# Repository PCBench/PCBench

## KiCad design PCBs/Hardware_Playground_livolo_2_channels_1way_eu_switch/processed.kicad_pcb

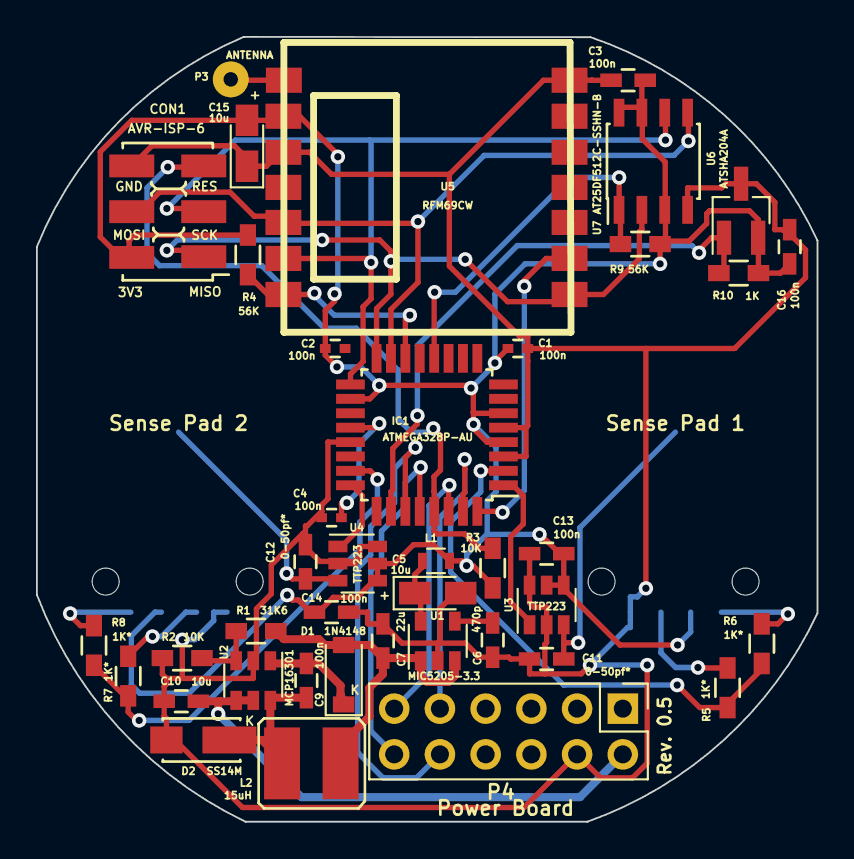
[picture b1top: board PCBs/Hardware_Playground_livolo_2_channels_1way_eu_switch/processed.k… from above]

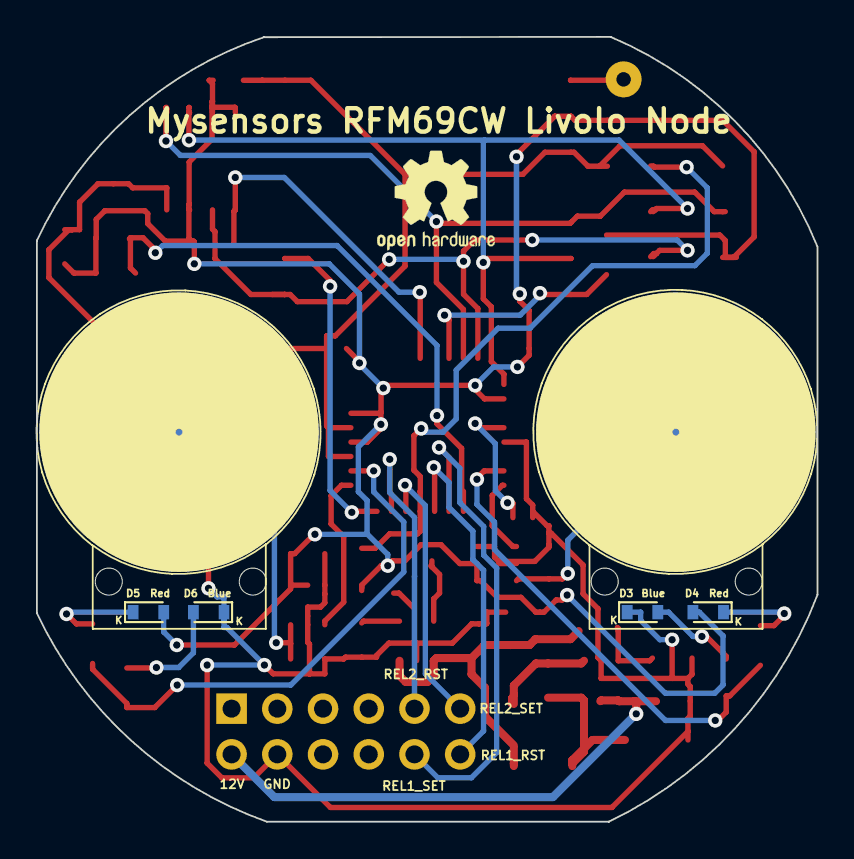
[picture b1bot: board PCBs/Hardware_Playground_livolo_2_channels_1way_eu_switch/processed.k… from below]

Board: 2 copper layers, 43.4 x 43.6 mm, 46 parts (4 on the bottom side), 33 nets.

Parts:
C1, C2, C4: 100n; C_0402
C3, C9, C13, C14, C16: 100n; C_0603_HandSoldering
C5, C15: 10u; CP_Tantalum_Case-R_EIA-2012-12_Wave
C6: 470p; C_0603_HandSoldering
C7: 22u; C_0603_HandSoldering
C10: 10u; C_0603_HandSoldering
C11, C12: 0-50pf*; C_0603_HandSoldering
CON1: AVR-ISP-6; AVR_ISP_SMT_Small_02x03
D1: 1N4148; SOD-123
D2: SS14M
D3, D6: Blue; D_0603
D4, D5: Red; D_0603
IC1: ATMEGA328P-AU; TQFP-32_7x7mm_Pitch0.8mm
L1: BLM18HE152SN1D; R_0603
L2: 15uH; VLCF4020T-150MR68
P1: Sense Pad 1; touch_pad_16mm
P2: Sense Pad 2; touch_pad_16mm
P3: ANTENNA; SolderWirePad_single_0-8mmDrill
P4: Power Board; Pin_Header_Straight_2x06_Pitch2.54mm
R1: 31K6; R_0603_HandSoldering
R2, R3: 10K; R_0603_HandSoldering
R4, R9: 56K; R_0603_HandSoldering
R5, R6, R7, R8: 1K*; R_0603_HandSoldering
R10: 1K; R_0603_HandSoldering
U1: MIC5205-3.3; SOT-23-5
U2: MCP16301; SOT-23-6
U3, U4: TTP223; SOT-23-6
U5: RFM69CW
U6: AT25DF512C-SSHN-B; SOIC-8_3.9x4.9mm_Pitch1.27mm
U7: ATSHA204A; SOT-23_Handsoldering

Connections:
+3V3: C1.1, C2.2, C3.2, C13.1, C14.1, C15.2, C16.2, CON1.2, D4.2, D5.2, IC1.4, IC1.6, IC1.18, L1.1, R3.1, R4.2, R9.1, R10.1, U3.4, U3.5, U4.4, U4.5, U5.2, U6.3, U6.7, U6.8, U7.2
/12Vcc: C10.1, P4.2, U2.4, U2.5
/ATSHA204A: IC1.26, R10.2, U7.1
/FLASH_SS: IC1.12, R9.2, U6.1
/INT: IC1.32, U5.9
/MISO: CON1.1, IC1.16, U5.8, U6.2
/MOSI: CON1.4, IC1.15, U5.5, U6.5
/RADIO_SS: IC1.14, R4.1, U5.7
/RESET: CON1.5, IC1.29, R3.2
/Relay1_Reset: IC1.28, P4.12
/Relay1_Set: IC1.27, P4.10
/Relay2_Reset: IC1.31, P4.9
/Relay2_Set: IC1.30, P4.11
/S1_LEDs: IC1.2, R5.2, R6.2
/S2_LEDs: IC1.23, R7.2, R8.2
/SCK: CON1.3, IC1.17, U5.6, U6.6
/TS1: IC1.1, U3.1
/TS2: IC1.24, U4.1
GND: C1.2, C3.1, C4.1, C5.2, C6.2, C7.2, C10.2, C11.2, C12.2, C13.2, C14.2, C15.1, C16.1, CON1.6, D2.2, D3.1, D6.1, IC1.3, IC1.5, IC1.21, P4.4, R2.1, U1.2, U2.2, U3.2, U3.6, U4.2, U4.6, U5.3, U5.14, U6.4, U7.3
unnamed: C4.2, IC1.20
unnamed: C5.1, L1.2, U1.5
unnamed: C6.1, U1.4
unnamed: C7.1, D1.2, L2.1, R1.2, U1.1, U1.3
unnamed: C9.1, D1.1, U2.1
unnamed: C9.2, D2.1, L2.2, U2.6
unnamed: C11.1, P1.1, U3.3
unnamed: C12.1, P2.1, U4.3
unnamed: D3.2, R7.1
unnamed: D4.1, R8.1
unnamed: D5.1, R6.1
unnamed: D6.2, R5.1
unnamed: P3.1, U5.1
unnamed: R1.1, R2.2, U2.3

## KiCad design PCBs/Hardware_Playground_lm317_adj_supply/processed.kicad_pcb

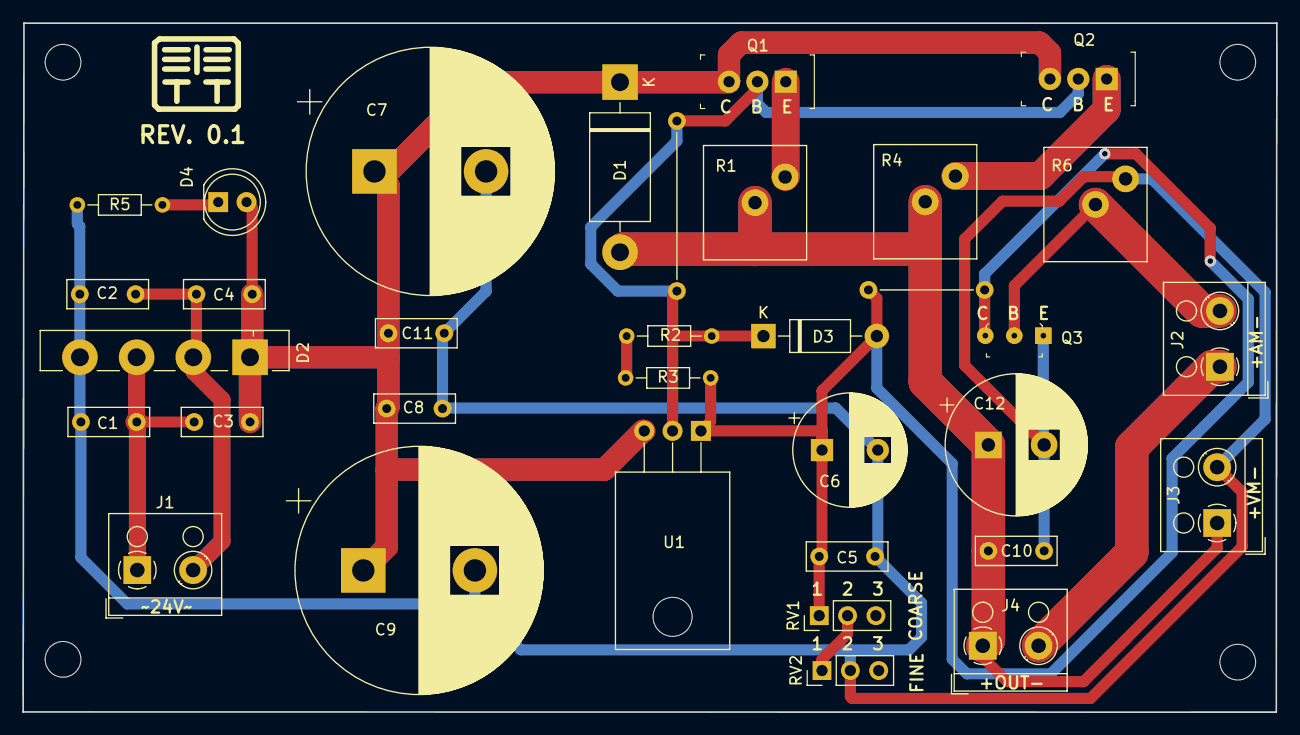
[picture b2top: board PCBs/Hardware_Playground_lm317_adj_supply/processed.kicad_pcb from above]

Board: 2 copper layers, 112.3 x 61.7 mm, 32 parts (0 on the bottom side), 14 nets.

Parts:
C1, C2, C3, C4, C5, C8, C10, C11: 0.1u/63V; C_Rect_L7.2mm_W2.5mm_P5.00mm_FKS2_FKP2_MKS2_MKP2
C6: 150u/50V; CP_Radial_D10.0mm_P5.00mm
C7, C9: 3300u/50V; CP_Radial_D22.0mm_P10.00mm_SnapIn
C12: 1000u/50V; CP_Radial_D12.5mm_P5.00mm
D1: MUR420; D_DO-201AD_P15.24mm_Horizontal
D2: GBU8M; Diode_Bridge_Vishay_GBU
D3: 1N4007; D_DO-41_SOD81_P10.16mm_Horizontal
D4: PWR_LED; LED_D5.0mm
J1: TR(24Vac); TerminalBlock_RND_205-00001_1x02_P5.00mm_Horizontal
J2: AMP_MEAS; TerminalBlock_RND_205-00001_1x02_P5.00mm_Horizontal
J3: VOLT_MEAS; TerminalBlock_RND_205-00001_1x02_P5.00mm_Horizontal
J4: V_REG_OUT; TerminalBlock_RND_205-00001_1x02_P5.00mm_Horizontal
Q1, Q2: TIP41C; TO-220-3
Q3: BC337; TO-92-3_Formed_Leads
R1, R4, R6: 0.12/5W; R_Radial_Power_L9.0mm_W10.0mm_Px2.70mm_Py2.30mm
R2, R3: 120; R_Axial_DIN0204_L3.6mm_D1.6mm_P7.62mm_Horizontal
R5: 6K8; R_Axial_DIN0204_L3.6mm_D1.6mm_P7.62mm_Horizontal
RV1: 5K; PinHeader_1x03_P2.54mm_Vertical
RV2: 500; PinHeader_1x03_P2.54mm_Vertical
U1: LM317; TO-220-3_Horizontal

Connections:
/V_REG_IN: C3.2, C4.1, C7.1, C8.1, C9.1, C11.1, D1.1, D2.1, D4.2, Q1.3, Q2.3, U1.3
GND: C1.2, C2.1, C5.2, C6.2, C7.2, C8.2, C9.2, C10.2, C11.2, C12.2, D2.4, J3.2, Q3.1, R5.2, R6.2, RV2.2
unnamed: C1.1, C3.1, D2.3, J1.1
unnamed: C2.2, C4.2, D2.2, J1.2
unnamed: C5.1, C6.1, D3.2, Q3.3, R3.2, RV1.1, U1.1
unnamed: C10.1, C12.1, D1.2, J3.1, J4.1, R1.1, R4.1
unnamed: D3.1, Q1.2, Q2.2, R2.1, U1.2
unnamed: D4.1, R5.1
unnamed: J2.1, J4.2
unnamed: J2.2, Q3.2, R6.1
unnamed: Q1.1, R1.2
unnamed: Q2.1, R4.2
unnamed: R2.2, R3.1
unnamed: RV1.2, RV2.1

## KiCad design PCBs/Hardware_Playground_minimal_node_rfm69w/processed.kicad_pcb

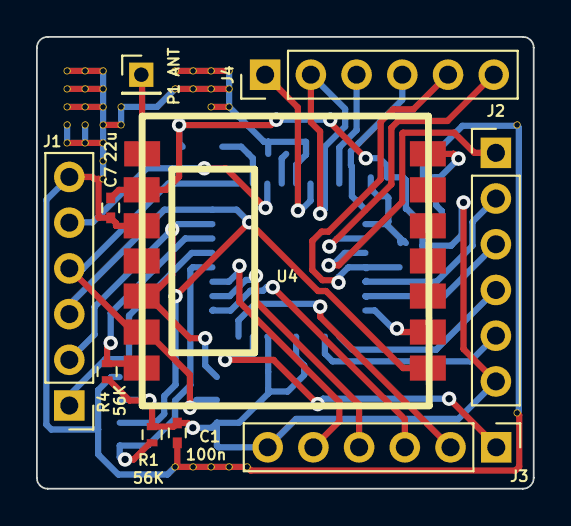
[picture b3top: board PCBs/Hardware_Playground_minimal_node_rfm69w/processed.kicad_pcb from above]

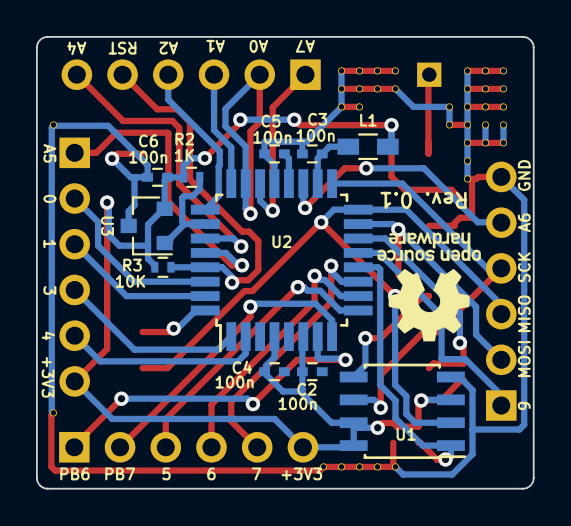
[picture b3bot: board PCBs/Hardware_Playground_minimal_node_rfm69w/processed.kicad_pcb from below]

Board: 2 copper layers, 27.6 x 25.1 mm, 57 parts (11 on the bottom side), 30 nets.

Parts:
C1, C2, C3, C4, C5, C6: 100n; C_0402
C7: 22u; C_0402
J1, J2, J3, J4: CONN_01X06; Pin_Header_Straight_1x06_Pitch2.54mm
L1: BLM18HE152; R_0603_HandSoldering
P1: ANT; Pin_Header_Straight_1x01_Pitch2.00mm
R1, R4: 56K; R_0402
R2: 1K; R_0402
R3: 10K; R_0402
U1: AT25DF512C; SOIC-8_3.9x4.9mm_Pitch1.27mm
U2: ATMEGA328P-AU; TQFP-32_7x7mm_Pitch0.8mm
U3: ATSHA204A; SOT-23
U4: RFM69CW
V8_3, V8_4, V8_5, V8_6, V8_7, V9_3, V9_4, V9_5, V9_6, V9_7, V10_3, V10_4, V10_5, V10_6, V10_7, V10_8, V10_9, V11_5, V11_6, V14_3, V14_4, V14_25, V15_3, V15_4, V15_25, V16_3, V16_4, V16_5, V16_25, V17_3, V17_4, V17_5, V17_25, V18_25, V33_6, V33_22: AUTO_VIA; VIA_MATRIX

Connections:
+3V3: C1.2, C2.1, C4.2, C6.1, C7.1, J2.6, J3.6, L1.2, R1.2, R2.2, R3.1, R4.2, U1.3, U1.7, U1.8, U2.4, U2.6, U3.2, U4.2
/7: J3.1, U2.7
/8: J3.2, U2.8
/19: J1.5, U2.19
/22: J4.1, U2.22
/ATSHA204A: R2.1, U2.26, U3.1
/MISO: J1.3, U1.2, U2.16, U4.8
/MOSI: J1.2, U1.5, U2.15, U4.5
/RFM69W_INT: U2.32, U4.9
/RFM69W_SS: R4.1, U2.14, U4.7
/RST: J4.5, R3.2, U2.29
/SCK: J1.4, U1.6, U2.17, U4.6
/SPI_FLASH_SS: R1.1, U1.1, U2.12
GND: C1.1, C3.1, C5.1, C6.2, C7.2, J1.6, U1.4, U2.21, U3.3, U4.3, U4.14, V8_3.1, V8_4.1, V8_5.1, V8_6.1, V8_7.1, V9_3.1, V9_4.1, V9_5.1, V9_6.1, V9_7.1, V10_3.1, V10_4.1, V10_5.1, V10_6.1, V10_7.1, V10_8.1, V10_9.1, V11_5.1, V11_6.1, V14_3.1, V14_4.1, V14_25.1, V15_3.1, V15_4.1, V15_25.1, V16_3.1, V16_4.1, V16_5.1, V16_25.1, V17_3.1, V17_4.1, V17_5.1, V17_25.1, V18_25.1, V33_6.1, V33_22.1
unnamed: C3.2, L1.1, U2.18
unnamed: C5.2, U2.20
unnamed: J1.1, U2.13
unnamed: J2.1, U2.28
unnamed: J2.2, U2.30
unnamed: J2.3, U2.31
unnamed: J2.4, U2.1
unnamed: J2.5, U2.2
unnamed: J3.3, U2.9
unnamed: J3.4, U2.10
unnamed: J3.5, U2.11
unnamed: J4.2, U2.23
unnamed: J4.3, U2.24
unnamed: J4.4, U2.25
unnamed: J4.6, U2.27
unnamed: P1.1, U4.1

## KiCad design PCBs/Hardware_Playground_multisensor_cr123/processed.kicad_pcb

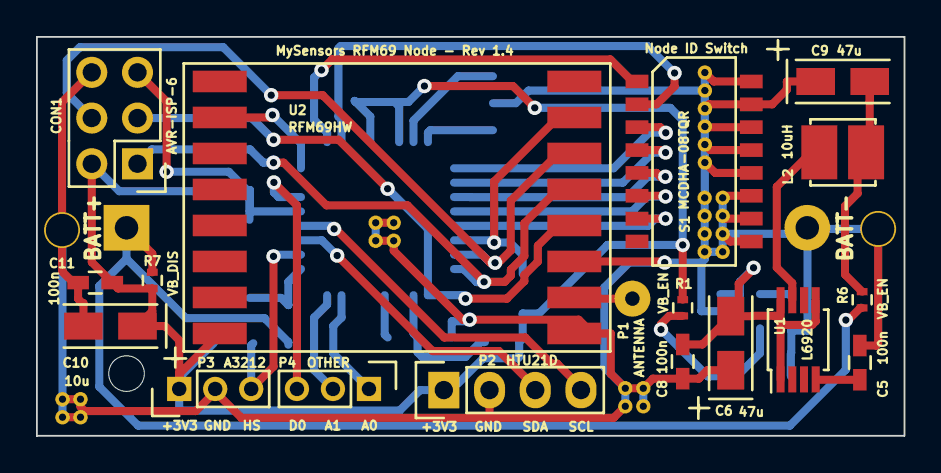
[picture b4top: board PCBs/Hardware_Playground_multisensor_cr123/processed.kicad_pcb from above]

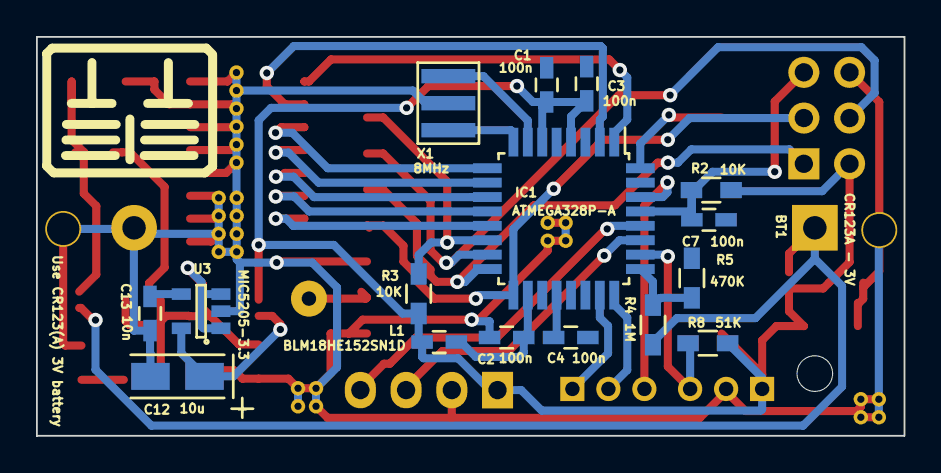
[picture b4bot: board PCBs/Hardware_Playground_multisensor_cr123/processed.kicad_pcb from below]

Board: 2 copper layers, 48.2 x 22.2 mm, 35 parts (17 on the bottom side), 34 nets.

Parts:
BT1: CR123A - 3V; CR123_holder
C1, C2, C3, C4, C5, C7, C8, C11: 100n; C_0603_HandSoldering
C6, C9: 47u; TantalC_SizeA_EIA-3216_Wave
C10, C12: 10u; TantalC_SizeA_EIA-3216_Wave
C13: 10n; C_0603_HandSoldering
CON1: AVR-ISP-6; Pin_Header_Straight_2x03
IC1: ATMEGA328P-A; TQFP-32_7x7mm_Pitch0.8mm
L1: BLM18HE152SN1D; C_0603_HandSoldering
L2: 10uH; DLJ-3015
P1: ANTENNA; SolderWirePad_single_0-8mmDrill
P2: HTU21D; Pin_Header_Straight_1x04
P3: A3212; Pin_Header_Straight_1x03_Pitch2.00mm
P4: OTHER; Pin_Header_Straight_1x03_Pitch2.00mm
R1, R6: VB_EN; R_0402
R2, R3: 10K; R_0603_HandSoldering
R4: 1M; R_0603_HandSoldering
R5: 470K; R_0603_HandSoldering
R7: VB_DIS; R_0402
R8: 51K; R_0603_HandSoldering
S1: MCDHA-08TQR; DIPSWITCH_SMD_1.27-16
U1: L6920; MSOP-8_3x3mm_Pitch0.65mm
U2: RFM69HW; RFM69HW_SMD_Handsoldering
U3: MIC5205-3.3; SOT-23-5
X1: 8MHz; ZTTCR-3

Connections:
+3V3: C1.1, C3.2, C10.1, C11.1, CON1.2, IC1.4, IC1.6, L1.1, P2.1, P3.1, R1.2, R2.1, R3.2, R7.1, R8.1, U2.8
/A0: IC1.23, P4.1
/A1: IC1.24, P4.2
/C0: IC1.1, S1.1
/C1: IC1.2, S1.2
/C2: IC1.9, S1.3
/C3: IC1.10, S1.4
/C4: IC1.11, S1.5
/C5: IC1.12, S1.6
/C6: IC1.13, S1.7
/D0: IC1.30, P4.3
/HALL_SENSOR: IC1.26, P3.3, R8.2
/INT: IC1.32, U2.2
/MISO: CON1.1, IC1.16, U2.13
/MOSI: CON1.4, IC1.15, U2.14
/RESET: C7.2, CON1.5, IC1.29, R2.2
/SCK: CON1.3, IC1.17, U2.12
/SCL: IC1.28, P2.4
/SDA: IC1.27, P2.3
/SS: IC1.14, R3.1, U2.15
/V_BATT: IC1.25, R4.1, R5.2
/V_BOOST_IN: C9.2, L2.2, R6.2
GND: BT1.2, C2.1, C5.2, C6.1, C8.2, C9.1, C10.2, C11.2, C12.2, C13.2, CON1.6, P2.2, P3.2, S1.9, S1.10, S1.11, S1.12, S1.13, S1.14, S1.15, S1.16, U2.9, U2.11, U3.2, X1.3
unnamed: BT1.1, R4.2, R6.1, R7.2
unnamed: C2.2, IC1.18, L1.2
unnamed: C4.2, IC1.20
unnamed: C5.1, U1.4
unnamed: C6.2, C8.1, U1.1, U1.5, U1.8, U3.1, U3.3
unnamed: C12.1, R1.1, U3.5
unnamed: C13.1, U3.4
unnamed: IC1.7, X1.2
unnamed: IC1.8, X1.1
unnamed: L2.1, U1.7
unnamed: P1.1, U2.10

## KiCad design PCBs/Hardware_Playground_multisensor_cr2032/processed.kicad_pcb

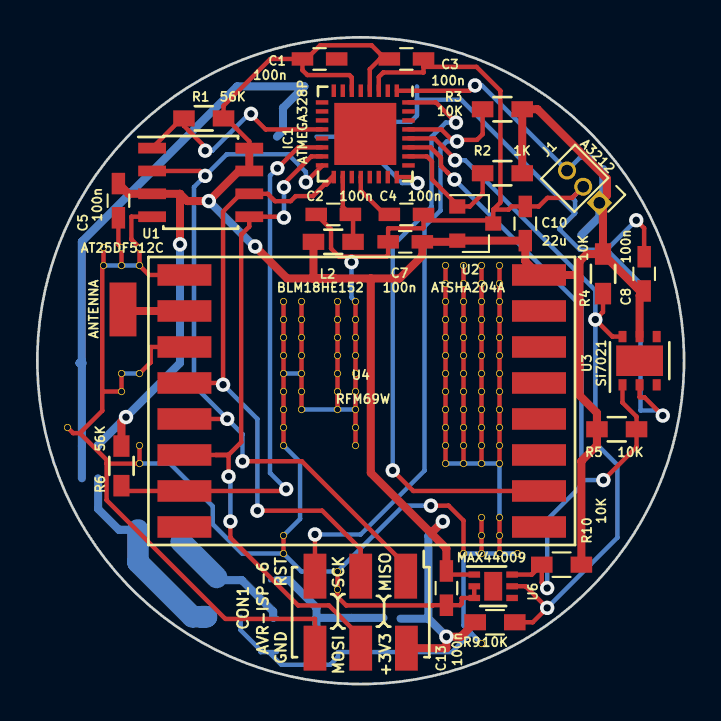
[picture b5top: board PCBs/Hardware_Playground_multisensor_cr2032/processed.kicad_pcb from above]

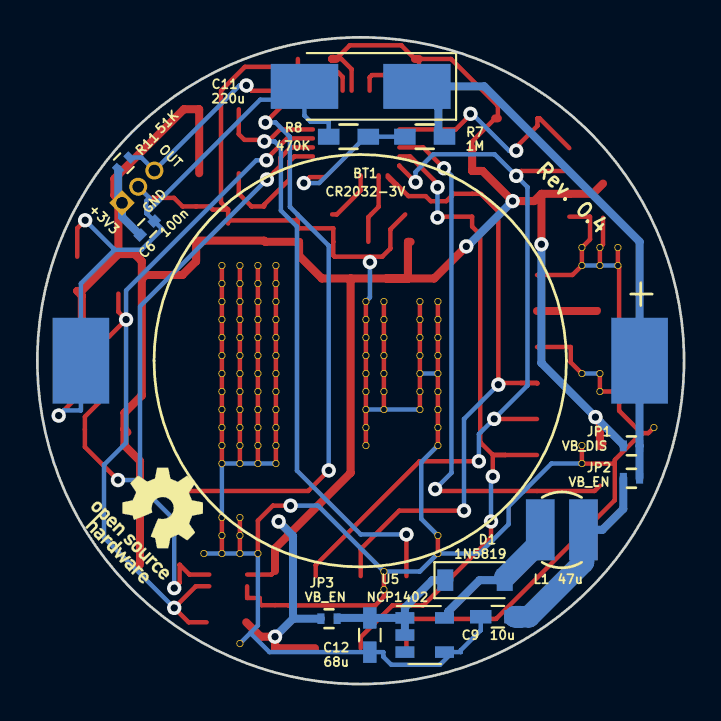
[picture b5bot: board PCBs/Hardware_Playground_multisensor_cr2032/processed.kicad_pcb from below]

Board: 2 copper layers, 35.9 x 35.9 mm, 146 parts (14 on the bottom side), 21 nets.

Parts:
BT1: CR2032-3V; CR2032_BATT-HOLDER_SMT_H2
C1, C2, C3, C4, C5, C7, C8, C13: 100n; C_0603_HandSoldering
C6: 100n; C_0402
C9: 10u; C_0603_HandSoldering
C10: 22u; C_0603_HandSoldering
C11: 220u; CP_Tantalum_Case-C_EIA-6032-28_Hand
C12: 68u; C_0603_HandSoldering
CON1: AVR-ISP-6; AVR_ISP_SMT_Small_02x03
D1: 1N5819; D_SOD-123
IC1: ATMEGA328P; QFN-32-1EP_5x5mm_Pitch0.5mm
J1: A3212; Pin_Header_Straight_1x03_Pitch1.27mm
JP1, JP3: VB_EN; R_0402
JP2: VB_DIS; R_0402
L1: 47u; SDR0302
L2: BLM18HE152; R_0603_HandSoldering
P1: ANTENNA; 1pin_smd_2mm
R1, R6: 56K; R_0603_HandSoldering
R2: 1K; R_0603_HandSoldering
R3, R4, R5, R9, R10: 10K; R_0603_HandSoldering
R7: 1M; R_0603_HandSoldering
R8: 470K; R_0603_HandSoldering
R11: 51K; R_0402
U1: AT25DF512C; SOIC-8_3.9x4.9mm_Pitch1.27mm
U2: ATSHA204A; SOT-23
U3: Si7021; DFN-6-1EP_3x3mm_Pitch0.95mm
U4: RFM69W; RFM69HW_SMD_Handsoldering
U5: NCP1402; SOT-23-5
U6: MAX44009; DFN-6-1EP_2x2mm_Pitch0.65mm
V2_22, V4_12, V4_13, V5_12, V5_13, V5_19, V5_20, V6_12, V6_13, V6_19, V6_23, V6_24, V14_15, V14_16, V14_17, V14_18, V14_19, V14_20, V14_21, V14_22, V14_23, V14_28, V14_29, V15_15, V15_16, V15_17, V15_18, V15_19, V15_20, V15_21, V17_15, V17_16, V17_17, V17_18, V17_19, V17_20, V17_21, V17_30, V17_31, V18_15, V18_16, V18_17, V18_18, V18_19, V18_20, V18_21, V18_22, V18_23, V23_13, V23_14, V23_15, V23_16, V23_17, V23_18, V23_19, V23_20, V23_21, V23_22, V23_23, V23_24, V24_13, V24_14, V24_15, V24_16, V24_17, V24_18, V24_19, V24_20, V24_21, V24_22, V24_23, V24_24, V24_29, V25_13, V25_14, V25_15, V25_16, V25_17, V25_18, V25_19, V25_20, V25_21, V25_22, V25_23, V25_24, V25_27, V25_28, V25_29, V25_34, V26_13, V26_14, V26_15, V26_16, V26_17, V26_18, V26_19, V26_20, V26_21, V26_22, V26_23, V26_24, V26_27, V26_28, V26_29, V27_29: AUTO_VIA; VIA_MATRIX

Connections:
+3V3: C1.1, C3.2, C5.2, C6.2, C7.1, C8.1, C10.1, C13.1, CON1.2, IC1.4, IC1.6, J1.1, JP2.2, JP3.2, L2.2, R1.2, R2.2, R3.1, R4.2, R5.2, R6.2, R9.2, R10.2, R11.1, U1.3, U1.7, U1.8, U2.2, U3.5, U4.8, U6.1
/A3212: IC1.1, J1.3, R11.2
/ATSHA204A: IC1.26, R2.1, U2.1
/MISO: CON1.1, IC1.16, U1.2, U4.13
/MOSI: CON1.4, IC1.15, U1.5, U4.14
/RFM69W_INT: IC1.32, U4.2
/RFM69W_SS: IC1.14, R6.1, U4.15
/RST: CON1.5, IC1.29, R3.2
/SCK: CON1.3, IC1.17, U1.6, U4.12
/SCL: IC1.28, R4.1, R9.1, U3.6, U6.5
/SDA: IC1.27, R5.1, R10.1, U3.1, U6.6
/SPI_FLASH_SS: IC1.12, R1.1, U1.1
/VB_IN: C9.2, JP1.1, L1.1
/V_BATT_MON: IC1.24, R7.1, R8.2
GND: BT1.2, C2.1, C3.1, C4.1, C5.1, C6.1, C7.2, C8.2, C9.1, C10.2, C11.2, C12.1, C13.2, CON1.6, IC1.3, J1.2, R8.1, U1.4, U2.3, U3.2, U4.9, U4.11, U5.4, U6.2, U6.3, V2_22.1, V4_12.1, V4_13.1, V5_12.1, V5_13.1, V5_19.1, V5_20.1, V6_12.1, V6_13.1, V6_19.1, V6_23.1, V6_24.1, V14_15.1, V14_16.1, V14_17.1, V14_18.1, V14_19.1, V14_20.1, V14_21.1, V14_22.1, V14_23.1, V14_28.1, V14_29.1, V15_15.1, V15_16.1, V15_17.1, V15_18.1, V15_19.1, V15_20.1, V15_21.1, V17_15.1, V17_16.1, V17_17.1, V17_18.1, V17_19.1, V17_20.1, V17_21.1, V17_30.1, V17_31.1, V18_15.1, V18_16.1, V18_17.1, V18_18.1, V18_19.1, V18_20.1, V18_21.1, V18_22.1, V18_23.1, V23_13.1, V23_14.1, V23_15.1, V23_16.1, V23_17.1, V23_18.1, V23_19.1, V23_20.1, V23_21.1, V23_22.1, V23_23.1, V23_24.1, V24_13.1, V24_14.1, V24_15.1, V24_16.1, V24_17.1, V24_18.1, V24_19.1, V24_20.1, V24_21.1, V24_22.1, V24_23.1, V24_24.1, V24_29.1, V25_13.1, V25_14.1, V25_15.1, V25_16.1, V25_17.1, V25_18.1, V25_19.1, V25_20.1, V25_21.1, V25_22.1, V25_23.1, V25_24.1, V25_27.1, V25_28.1, V25_29.1, V25_34.1, V26_13.1, V26_14.1, V26_15.1, V26_16.1, V26_17.1, V26_18.1, V26_19.1, V26_20.1, V26_21.1, V26_22.1, V26_23.1, V26_24.1, V26_27.1, V26_28.1, V26_29.1, V27_29.1
unnamed: BT1.1, C11.1, JP1.2, JP2.1, R7.2
unnamed: C2.2, IC1.18, L2.1
unnamed: C4.2, IC1.20
unnamed: C12.2, D1.1, JP3.1, U5.1, U5.2
unnamed: D1.2, L1.2, U5.5
unnamed: P1.1, U4.10

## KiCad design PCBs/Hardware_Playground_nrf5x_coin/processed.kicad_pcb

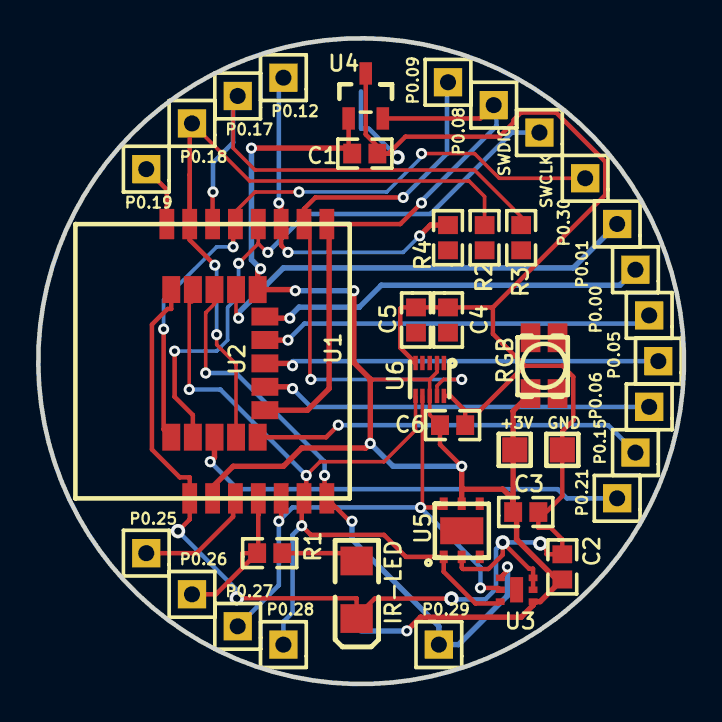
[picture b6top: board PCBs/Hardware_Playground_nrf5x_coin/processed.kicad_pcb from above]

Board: 2 copper layers, 35.9 x 35.9 mm, 41 parts (0 on the bottom side), 23 nets.

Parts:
+3V: PAD-1.4X1.4-ALPS-H1.6
C1, C2, C3, C4, C5, C6: 100n; 0603
CR2032-3V: CR2032-BS-6-1; BATTERY-3
GND: PAD-1.4X1.4-ALPS-H1.6
IR-LED: IR LED; LED-1206
P0.00: P0.00; HDR-1X1_2.54
P0.01: P0.01; HDR-1X1_2.54
P0.05: P0.05; HDR-1X1_2.54
P0.06: P0.06; HDR-1X1_2.54
P0.08: P0.08; HDR-1X1_2.54
P0.09: P0.09; HDR-1X1_2.54
P0.12: P0.12; HDR-1X1_2.54
P0.15: P0.15; HDR-1X1_2.54
P0.17: P0.17; HDR-1X1_2.54
P0.18: P0.18; HDR-1X1_2.54
P0.19: P0.19; HDR-1X1_2.54
P0.21: P0.21; HDR-1X1_2.54
P0.25: P0.25; HDR-1X1_2.54
P0.26: P0.26; HDR-1X1_2.54
P0.27: P0.27; HDR-1X1_2.54
P0.28: P0.28; HDR-1X1_2.54
P0.29: P0.29; HDR-1X1_2.54
P0.30: P0.30; HDR-1X1_2.54
R1, R2, R3, R4: 100Ω; 0603
RGB: ASMB-MTB1-0A3A2; ASMB-MTB1-0A3A2-RGB-LED
SWCLK: SWCLK; HDR-1X1_2.54
SWDIO: SWDIO; HDR-1X1_2.54
U1: PTR5518
U2: ANT; HOLYIOT NRF52832
U3: MAX44009EDT+; MAXM-D622N+4_V
U4: DRV5032AJDBZR; SOT-23(SOT-23-3)
U5: HTU21D; DFN-6-EP
U6: MAG3110FCR1; DFN-10

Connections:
+3V: +3V.1, C1.2, C2.2, C3.1, C6.1, CR2032-3V.1, RGB.1, U1.P$10, U2.11, U3.1, U4.1, U5.5, U6.2, U6.8
GND: C1.1, C2.1, C3.2, C4.1, C5.1, C6.2, CR2032-3V.2, GND.1, IR-LED.2, U1.P$9, U2.15, U3.2, U3.3, U4.3, U5.2, U6.5, U6.10
LED1_1: IR-LED.1, R1.2
P0.00: P0.00.1, U2.9
P0.01: P0.01.1, U2.10
P0.05: P0.05.1, U2.8
P0.06: P0.06.1, U2.7
P0.08: P0.08.1, U1.P$1, U2.6, U4.2
P0.09: P0.09.1, U1.P$2, U6.9
P0.12: P0.12.1, R4.2, U1.P$3
P0.15: P0.15.1, U2.5
P0.17: P0.17.1, R3.2, U1.P$6
P0.18: P0.18.1, R2.2, U1.P$7, U2.4
P0.19: P0.19.1, U1.P$8
P0.21: P0.21.1, U2.3
P0.25: P0.25.1, U1.P$11
P0.26: P0.26.1, R1.1, U1.P$12
P0.27: P0.27.1, U1.P$13, U3.5, U5.6, U6.7
P0.28: P0.28.1, U1.P$14, U2.14, U3.6, U5.1, U6.6
P0.29: P0.29.1, U1.P$15, U2.13, U3.4
P0.30: P0.30.1, U2.12
SWCLK: SWCLK.1, U1.P$5, U2.1
SWDIO: SWDIO.1, U1.P$4, U2.2

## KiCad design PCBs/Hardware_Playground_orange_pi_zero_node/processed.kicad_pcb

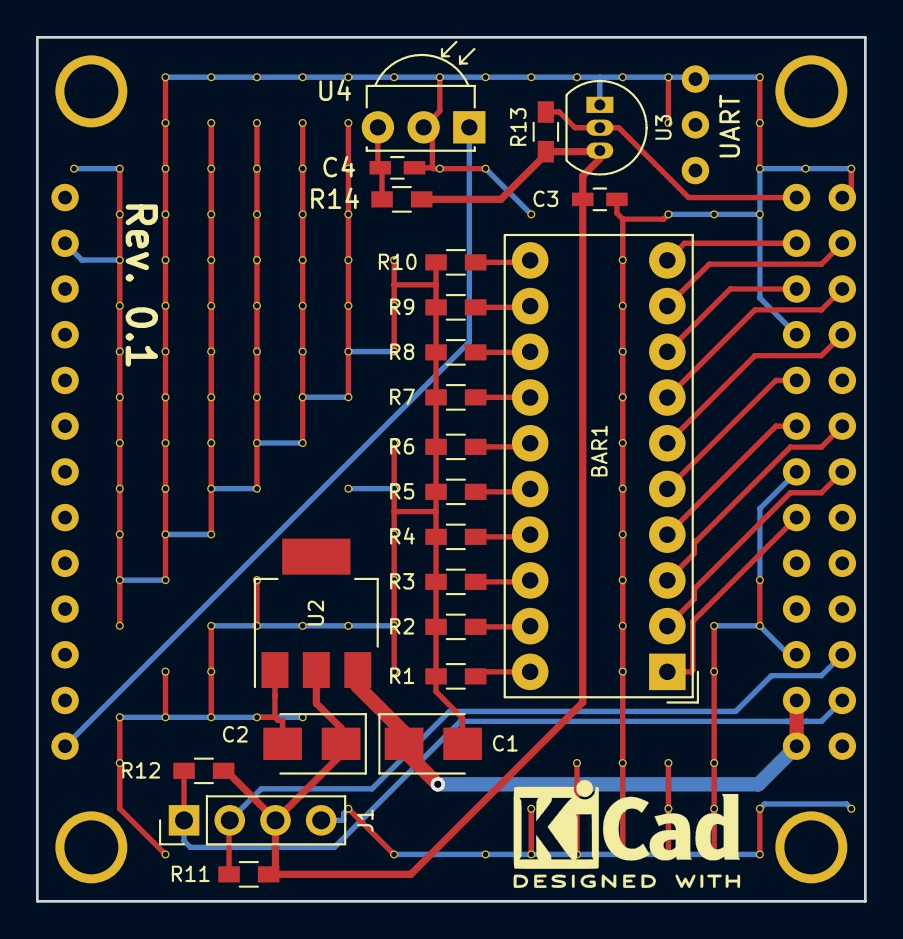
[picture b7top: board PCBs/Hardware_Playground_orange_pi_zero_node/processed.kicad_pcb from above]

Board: 2 copper layers, 46.0 x 48.0 mm, 163 parts (0 on the bottom side), 28 nets.

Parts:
BAR1: HDSP-4850_2; HDSP-4850
C1, C2: 22u; CP_Tantalum_Case-B_EIA-3528-21_Wave
C3, C4: 100n; C_0603_HandSoldering
J1: Conn_01x04; Pin_Header_Straight_1x04_Pitch2.54mm
R1, R2, R3, R4, R5, R6, R7, R8, R9, R10: 330; R_0603_HandSoldering
R11, R12, R13: 4K7; R_0603_HandSoldering
R14: 100; R_0603_HandSoldering
U1: orange_pi_zero; orangepi-zero
U2: AMS1117-3.3; SOT-223
U3: DS18B20; TO-92_Inline_Narrow_Oval
U4: TSOP343xx; IRReceiver_Vishay_MOLD-3pin
V1_3, V2_3, V2_4, V2_5, V2_6, V2_7, V2_8, V2_9, V2_10, V2_11, V2_12, V2_13, V2_15, V2_16, V3_1, V3_2, V3_3, V3_4, V3_5, V3_6, V3_7, V3_8, V3_9, V3_10, V3_11, V3_12, V3_14, V3_15, V3_18, V4_1, V4_2, V4_3, V4_4, V4_5, V4_6, V4_7, V4_8, V4_9, V4_10, V4_11, V4_13, V4_14, V4_15, V5_1, V5_2, V5_3, V5_4, V5_5, V5_6, V5_7, V5_8, V5_9, V5_10, V5_12, V5_13, V5_15, V6_1, V6_2, V6_3, V6_4, V6_5, V6_6, V6_7, V6_8, V6_9, V6_13, V6_15, V7_1, V7_2, V7_3, V7_4, V7_5, V7_6, V7_7, V7_8, V7_10, V7_13, V7_17, V8_1, V8_5, V8_6, V8_7, V8_9, V8_10, V8_11, V8_12, V8_13, V8_14, V8_18, V9_1, V9_3, V10_1, V10_3, V10_18, V11_1, V11_4, V11_17, V11_18, V12_1, V12_16, V12_17, V12_18, V13_1, V13_5, V13_6, V13_7, V13_8, V13_9, V13_10, V13_11, V13_12, V13_13, V13_14, V13_16, V13_17, V13_18, V14_1, V14_2, V14_4, V14_16, V14_17, V14_18, V15_4, V15_13, V15_14, V15_16, V15_17, V15_18, V16_1, V16_2, V16_3, V16_4, V16_12, V16_13, V16_17, V16_18, V17_3, V18_3, V18_17: AUTO_VIA; VIA_MATRIX

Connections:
+3V3: C2.1, C3.2, J1.3, R11.2, R12.2, R13.2, R14.2, U2.2, U3.3
+5V: C1.1, U1.102, U1.104, U2.3
GND: C1.2, C2.2, C3.1, C4.1, J1.4, R1.1, R2.1, R3.1, R4.1, R5.1, R6.1, R7.1, R8.1, R9.1, R10.1, U1.2, U1.106, U1.114, U1.120, U1.125, U1.201, U2.1, U3.1, U4.2, V1_3.1, V2_3.1, V2_4.1, V2_5.1, V2_6.1, V2_7.1, V2_8.1, V2_9.1, V2_10.1, V2_11.1, V2_12.1, V2_13.1, V2_15.1, V2_16.1, V3_1.1, V3_2.1, V3_3.1, V3_4.1, V3_5.1, V3_6.1, V3_7.1, V3_8.1, V3_9.1, V3_10.1, V3_11.1, V3_12.1, V3_14.1, V3_15.1, V3_18.1, V4_1.1, V4_2.1, V4_3.1, V4_4.1, V4_5.1, V4_6.1, V4_7.1, V4_8.1, V4_9.1, V4_10.1, V4_11.1, V4_13.1, V4_14.1, V4_15.1, V5_1.1, V5_2.1, V5_3.1, V5_4.1, V5_5.1, V5_6.1, V5_7.1, V5_8.1, V5_9.1, V5_10.1, V5_12.1, V5_13.1, V5_15.1, V6_1.1, V6_2.1, V6_3.1, V6_4.1, V6_5.1, V6_6.1, V6_7.1, V6_8.1, V6_9.1, V6_13.1, V6_15.1, V7_1.1, V7_2.1, V7_3.1, V7_4.1, V7_5.1, V7_6.1, V7_7.1, V7_8.1, V7_10.1, V7_13.1, V7_17.1, V8_1.1, V8_5.1, V8_6.1, V8_7.1, V8_9.1, V8_10.1, V8_11.1, V8_12.1, V8_13.1, V8_14.1, V8_18.1, V9_1.1, V9_3.1, V10_1.1, V10_3.1, V10_18.1, V11_1.1, V11_4.1, V11_17.1, V11_18.1, V12_1.1, V12_16.1, V12_17.1, V12_18.1, V13_1.1, V13_5.1, V13_6.1, V13_7.1, V13_8.1, V13_9.1, V13_10.1, V13_11.1, V13_12.1, V13_13.1, V13_14.1, V13_16.1, V13_17.1, V13_18.1, V14_1.1, V14_2.1, V14_4.1, V14_16.1, V14_17.1, V14_18.1, V15_4.1, V15_13.1, V15_14.1, V15_16.1, V15_17.1, V15_18.1, V16_1.1, V16_2.1, V16_3.1, V16_4.1, V16_12.1, V16_13.1, V16_17.1, V16_18.1, V17_3.1, V18_3.1, V18_17.1
unnamed: BAR1.1, U1.112
unnamed: BAR1.2, U1.113
unnamed: BAR1.3, U1.115
unnamed: BAR1.4, U1.116
unnamed: BAR1.5, U1.118
unnamed: BAR1.6, U1.119
unnamed: BAR1.7, U1.121
unnamed: BAR1.8, U1.122
unnamed: BAR1.9, U1.123
unnamed: BAR1.10, U1.124
unnamed: BAR1.11, R10.2
unnamed: BAR1.12, R9.2
unnamed: BAR1.13, R8.2
unnamed: BAR1.14, R7.2
unnamed: BAR1.15, R6.2
unnamed: BAR1.16, R5.2
unnamed: BAR1.17, R4.2
unnamed: BAR1.18, R3.2
unnamed: BAR1.19, R2.2
unnamed: BAR1.20, R1.2
unnamed: C4.2, R14.1, U4.3
unnamed: J1.1, R12.1, U1.103
unnamed: J1.2, R11.1, U1.105
unnamed: R13.1, U1.126, U3.2
unnamed: U1.13, U4.1
